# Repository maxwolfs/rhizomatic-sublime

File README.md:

# The rhizomatic sublime
### Searching for aesthetic transcendence in digital transience
Process and documentation of a research by [Max Wolfs](https://github.com/maxwolfs) and [Alexander Lehmann](https://github.com/bsplt).

### Rhizm

We object to the mundane paradigm of Human-Computer-Interaction and demand a Human-Human-Interaction. It's pyhsicial, it's intimate, it's exciting. Rhizm is a device in the shape of a credit card that connects over a satisfying magnetic click. Caution: Hands may touch. The connection of two cards creates a new bond in a decentralized social mesh network. Combined with a web interface that shows the verified encrypted interactions, Rhizm can be used for many different scenarios in which a physicial interaction between nodes must be safe. Or appealing. We understand our project as fundamental research in times of disbelief and scepsis among the realms of new technologies and social media. We want to commit ourselves to the power of open source platforms. Through social sandboxes like Rhizm a diverse variety of use cases such as self deployable social networks depending on real human interactions are possible.

Inject - Exhaust - Dissipate

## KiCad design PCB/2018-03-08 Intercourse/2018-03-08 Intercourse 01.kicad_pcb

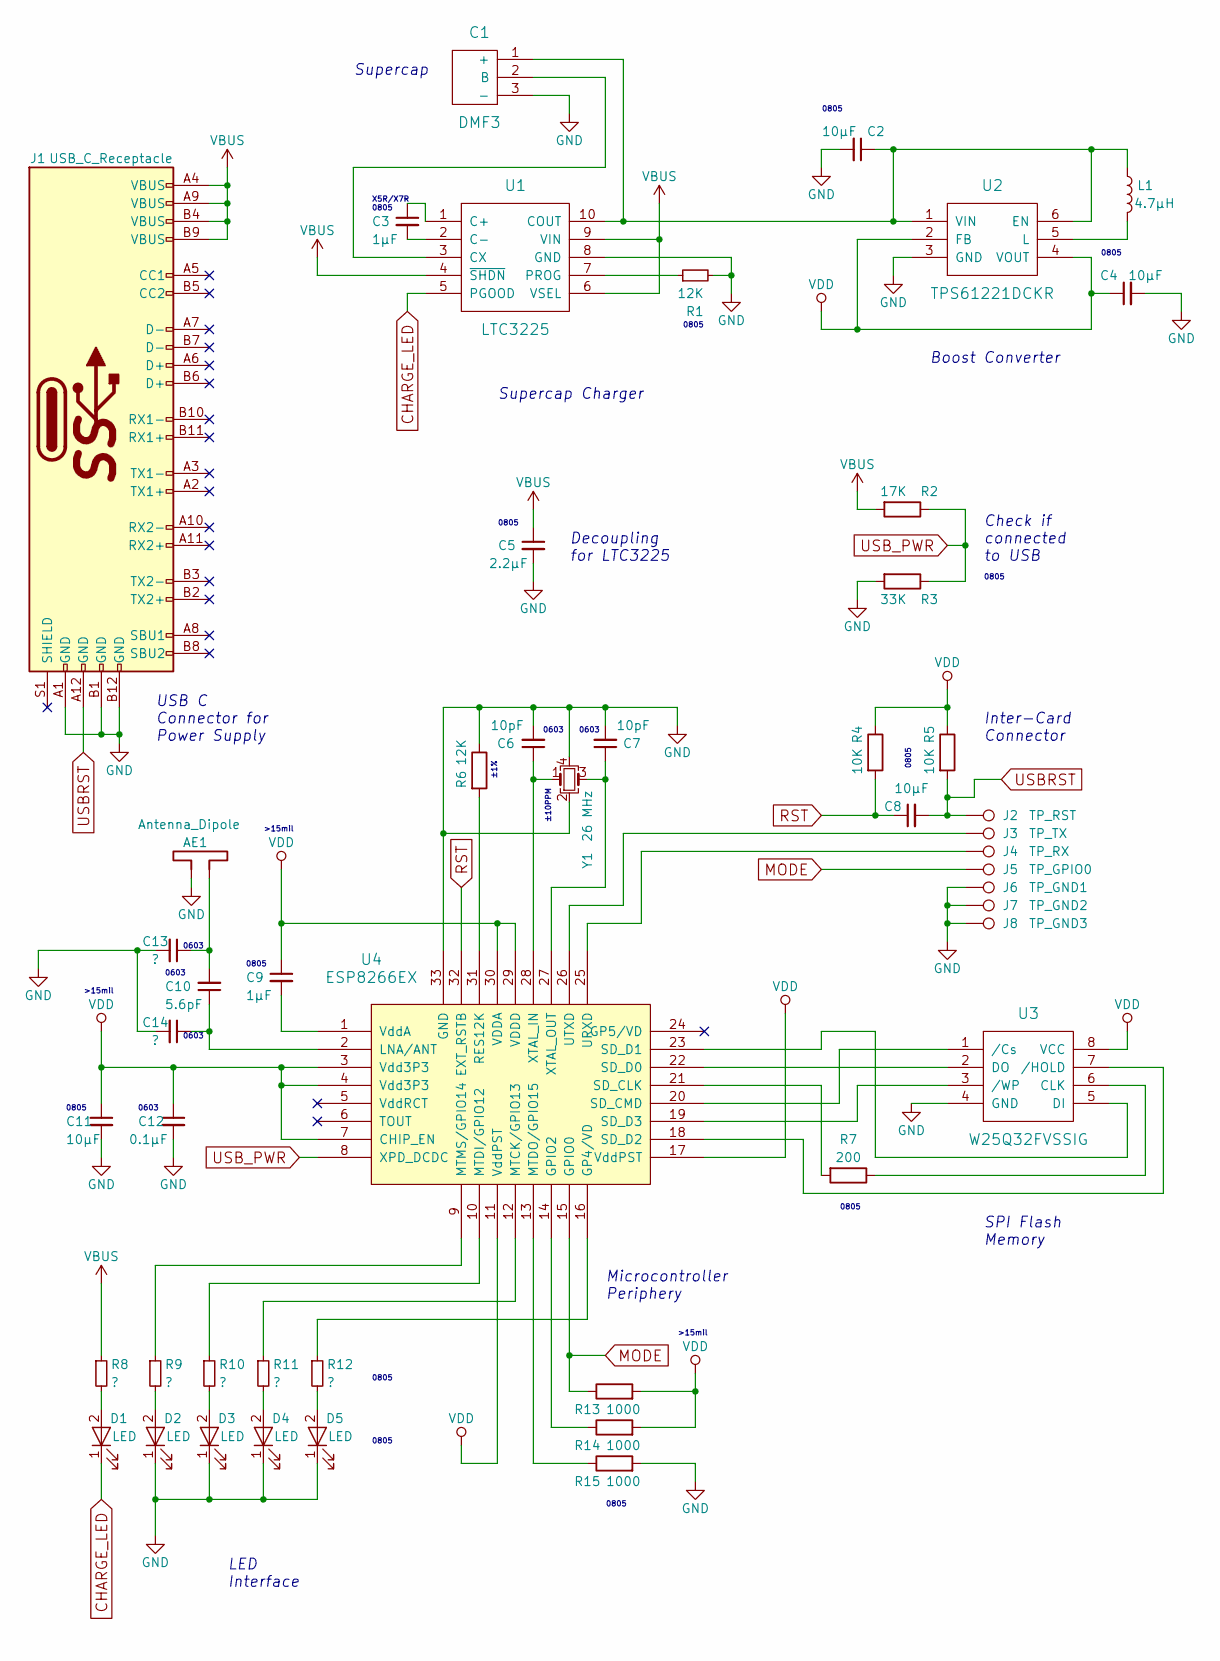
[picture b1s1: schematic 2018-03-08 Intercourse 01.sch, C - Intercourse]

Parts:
AE1: Antenna_Dipole; AN91445_47_mils
C1: DMF3; Murata_DMF3Z
C2, C4, C8, C11: 10μF; C_0805_HandSoldering
C3: 1μF; C_0805_HandSoldering
C5: 2.2μF; C_0805_HandSoldering
C6, C7: 10pF; C_0603_HandSoldering
C9: 1μF; C_0603_HandSoldering
C10: 5.6pF; C_0603_HandSoldering
C12: 0.1μF; C_0603_HandSoldering
C13, C14: ?; C_0603_1608Metric_Pad1.05x0.95mm_HandSolder
D1, D2, D3, D4, D5: LED; LED_0805_HandSoldering
J1: USB_C_Receptacle; USB_C_Receptacle_Amphenol_12401610E4-2A
J2: TP_RST; C_Connector_2mm
J3: TP_TX; C_Connector_2mm
J4: TP_RX; C_Connector_2mm
J5: TP_GPIO0; Measurement_Point_Round-SMD-Pad_Small
J6: TP_GND1; C_Connector_2mm
J7: TP_GND2; C_Connector_2mm
J8: TP_GND3; C_Connector_2mm
L1: 4.7μH; LQH3NPN4R7MJRL
R1, R6: 12K; R_0805_HandSoldering
R2: 17K; R_0805_HandSoldering
R3: 33K; R_0805_HandSoldering
R4, R5: 10K; R_0805_HandSoldering
R7: 200; R_0805_HandSoldering
R8, R9, R10, R11, R12: ?; R_0805_HandSoldering
R13, R14, R15: 1000; R_0805_HandSoldering
U1: LTC3225; DFN-10-1EP_2x3mm_Pitch0.5mm
U2: TPS61221DCKR; sc_70-6
U3: W25Q32FVSSIG; SOIC-8_3.9x4.9mm_Pitch1.27mm
U4: ESP8266EX; QFN-32-1EP_5x5mm_Pitch0.5mm
Y1: 26 MHz; Crystal_SMD_Abracon_ABM8G-4pin_3.2x2.5mm

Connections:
CHARGE_LED: D1.1 (K), U1.5 (PGOOD)
GND: AE1.1, C1.3 (-), C2.2, C4.2, C5.2, C6.2, C7.2, C11.2, C12.2, C13.2, C14.2, D2.1 (K), D3.1 (K), D4.1 (K), D5.1 (K), J1.A1 (GND), J1.B1 (GND), J1.B12 (GND), J6.1, J7.1, J8.1, R1.2, R3.2, R6.1, R15.2, U1.8 (GND), U2.3 (GND), U3.4 (GND), U4.33 (GND), Y1.2, Y1.4
MODE: J5.1, R13.1, U4.15 (GPIO0)
unnamed: AE1.2, C10.2, C13.1
unnamed: C1.1 (+), C2.1, L1.1, U1.10 (COUT), U2.1 (VIN), U2.6 (EN)
unnamed: C1.2 (B), U1.3 (CX)
unnamed: C3.1, U1.1 (C+)
unnamed: C3.2, U1.2 (C-)
unnamed: C6.1, U4.28 (XTAL_IN), Y1.1
unnamed: C7.1, U4.27 (XTAL_OUT), Y1.3
unnamed: C9.2, U4.1 (VddA)
unnamed: C10.1, C14.1, U4.2 (LNA/ANT)
unnamed: D1.2 (A), R8.2
unnamed: D2.2 (A), R9.2
unnamed: D3.2 (A), R10.2
unnamed: D4.2 (A), R11.2
unnamed: D5.2 (A), R12.2
unnamed: J3.1, U4.26 (UTXD)
unnamed: J4.1, U4.25 (URXD)
unnamed: L1.2, U2.5 (L)
unnamed: R1.1, U1.7 (PROG)
unnamed: R6.2, U4.31 (RES12K)
unnamed: R7.1, U3.6 (CLK)
unnamed: R7.2, U4.21 (SD_CLK)
unnamed: R9.1, U4.9 (MTMS/GPIO14)
unnamed: R10.1, U4.10 (MTDI/GPIO12)
unnamed: R11.1, U4.12 (MTCK/GPIO13)
unnamed: R12.1, U4.16 (GP4/VD)
unnamed: R14.1, U4.14 (GPIO2)
unnamed: R15.1, U4.13 (MTDO/GPIO15)
unnamed: U3.1 (/Cs), U4.20 (SD_CMD)
unnamed: U3.2 (DO), U4.22 (SD_D0)
unnamed: U3.3 (/WP), U4.19 (SD_D3)
unnamed: U3.5 (DI), U4.23 (SD_D1)
unnamed: U3.7 (/HOLD), U4.18 (SD_D2)
RST: C8.1, R4.2, U4.32 (EXT_RSTB)
USBRST: C8.2, J1.A12 (GND), J2.1, R5.2
USB_PWR: R2.1, R3.1, U4.8 (XPD_DCDC)
VBUS: C5.1, J1.A4 (VBUS), J1.A9 (VBUS), J1.B4 (VBUS), J1.B9 (VBUS), R2.2, R8.1, U1.4 (~SHDN), U1.6 (VSEL), U1.9 (VIN)
VDD: C4.1, C9.1, C11.1, C12.1, R4.1, R5.1, R13.2, R14.2, U2.2 (FB), U2.4 (VOUT), U3.8 (VCC), U4.3 (Vdd3P3), U4.4 (Vdd3P3), U4.7 (CHIP_EN), U4.11 (VddPST), U4.17 (VddPST), U4.29 (VDDD), U4.30 (VDDA)

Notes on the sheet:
Decoupling for LTC3225
Supercap Charger
Boost Converter
USB C Connector for Power Supply
Supercap
Microcontroller Periphery
SPI Flash Memory
Inter-Card Connector
Check if connected to USB
LED Interface
0805
±10PPM
±1%
>15mil
0603
0805
X5R/X7R 0805

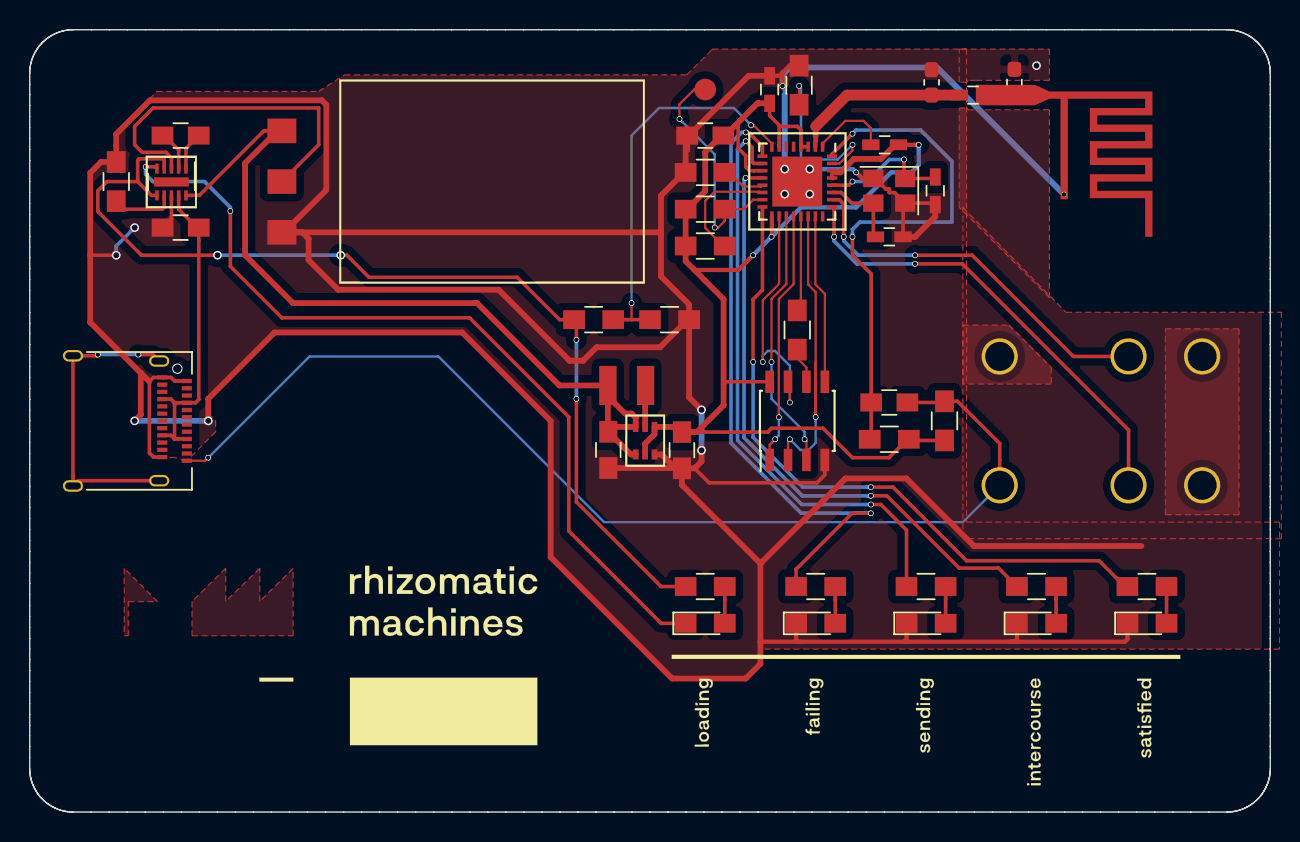
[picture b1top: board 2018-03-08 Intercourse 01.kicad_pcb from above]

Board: 2 copper layers, 85.6 x 54.0 mm, 49 parts (0 on the bottom side), 40 nets.

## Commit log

2017-07-03 :circus_tent: Added .gitattributes
2017-07-03 First TXT
2017-07-03 REWRITE readme
2017-07-03 Modified
2017-07-03 Modification
2017-07-03 Structure
2017-07-03 Minor changes and content update
2017-07-03 typo
2017-07-09 small issues
2017-07-11 english and link
2017-07-11 added idea
2017-07-11 typos
2017-07-11 subtle change
2017-07-11 added link
2017-07-19 Create Kunst oder Cash Concept
2017-07-19 Rename Kunst oder Cash to Kunst oder Cash.md
2017-07-19 Update Link & Title: Kunst oder Cash
2017-08-02 Create dystopianFuture.md
    Random Thoughts w.i.p.
2017-10-16 backup
2017-10-16 Create genesis
2017-10-16 change
2017-10-16 images
2017-10-24 UPDATE: Folder Strtucture and Link List
2017-10-24 link
2017-10-24 UPDATE: AI Trojan Horse Idea
2017-10-24 ADD Pdf proposal
2017-10-27 ADD HEC Sponsorship & Nitinol Tech Infos
2017-10-27 mpu test
2017-10-27 proposals
2017-10-31 ADD Nitinol Link
2017-11-01 new links
2017-11-01 removed conflicts
2017-11-07 ADD tech link
2017-11-10 New Link
2017-11-14 joints
2017-11-14 tree stuff links
2017-11-14 hello?
2017-11-26 NN Sim 1
2017-12-01 update links
2018-02-28 Update Budget
2018-03-07 created BOM
2018-03-07 updated BOM
2018-03-08 Add links
2018-03-08 Add Kicad Project
2018-03-13 Update Schematics
    * Add SPI Wiring
2018-03-13 Update Schematics
    * Finish ESP8266EX
2018-03-13 added spi flash
2018-03-13 Update
    Add Hardware Reference Sheet
2018-03-13 added supercap
2018-03-13 added usb
2018-03-14 Equation link
2018-03-15 added supercap charger
2018-03-15 added charge pump into schematic
2018-03-15 Update Schematic
    * Add missing Cap Values
2018-03-15 charge pump done
2018-03-15 added boost converter
2018-03-16 added TPS61221DCKR
2018-03-16 added booster circuit to schematic
2018-03-16 layout
2018-03-16 plain schematic finished and beautified
2018-03-17 link to programming resource
2018-03-17 started adding dev and conn pins
    not complete
2018-03-19 schematic edits
    * added NCs
    * clean up
2018-03-19 clean up schematic
    * added connector
    * changed labels
    * made some stuff cleaner
2018-03-19 further cleaning
    * cleaned up
    * added todos
2018-03-19 added examle for ESP8266 schematic
2018-03-20 changes labels
    Because I like them better ...
2018-03-20 added todo list
2018-03-21 added design link
2018-03-21 added reset rc filter circuit
2018-03-21 added leds to schematic
2018-03-21 added usb c recaptable
2018-03-21 Add links for writing to FLASH / EEPROM
2018-03-21 Replace BOM Table with Mouser BOM Link
2018-03-21 changed open drain circuit on charger
2018-03-21 corrected capacitors on esp8266ex
2018-03-21 minor fixes
2018-03-22 added esp8266 pin references
2018-03-22 finailzed schematic with annotations
2018-03-22 Update Paths
2018-03-22 Add Antenna Library
2018-03-22 updated library paths
2018-03-22 created additional footprints and completed footprint reference
2018-03-23 created netlist and created pcb
2018-03-23 Add Design Layout Template
2018-03-23 printability
2018-03-23 Add Max Design
2018-03-23 Add PDF Design
2018-03-23 alex sein design
2018-03-23 plotted schematic
2018-03-23 started pcb layout
2018-03-23 Add Logo AI #nocad
2018-03-24 backup of layouting process
2018-03-24 added link to kicad designing
2018-03-24 backup pcb layout
2018-03-25 advanced layout, backuping
2018-03-25 ready to route
2018-03-26 layout 01 before drc
2018-03-26 drc complete
2018-03-27 created graphic layout and edited it into pcb
2018-03-27 logo fix
2018-03-27 gerber files
2018-03-27 don't know what I changed
2018-03-30 generative experiment 1
2018-03-31 update and clean up
    deleted deprecated tables
2018-03-31 started seroius logo sketches
2018-03-31 major cleanup and moving around
2018-03-31 deleted unnecessary files
2018-03-31 explanation
2018-04-07 FIX 2 PCBnew Errors
    * Supercap + -> Henry
    * SupercapCharger GND Connection
2018-04-09 fonts
2018-04-09 layouten
2018-04-09 clean pcb is fine
2018-04-09 added layout and created gerber files
2018-04-10 Add USBRST Connection on .sch & .pcb
2018-04-10 rev3
2018-04-10 rev3 fixed via position
2018-04-11 Add Test Code
2018-04-12 Update Links
    * Add RF PCB Guidelines Link
2018-04-15 Add esp-http-post code
2018-04-16 Dataviz and Clean Up
2018-04-16 Update Readme and demo esp code
2018-04-17 Update Presentation Code
2018-04-18 Add Brochure
2018-04-18 dataviz looks good!
2018-04-18 cleanup and presentation
2018-04-19 backup and fixes
2018-04-19 Add userflow
2018-04-19 broschure
2018-04-19 ausgeschossen
2018-04-20 notizen
2018-04-20 Update Codes
2018-04-22 Add HEC application
2018-04-22 flowchart
2018-04-22 edit
2018-04-22 application pdf
2018-05-08 update brochure folder
2018-05-08 Add conference document
2018-05-08 change title
2018-05-08 Auto stash before merge of "master" and "origin/master"
2018-05-08 cleanup
2018-05-08 Conference
2018-05-08 updatze
2018-05-25 Add web documentation
2018-05-27 add conference pptx
2018-08-08 update scenarios
2018-11-10 update presentation
2018-11-22 update foto
2018-11-22 presentation backup
2018-11-22 update ppt
2018-11-23 add kicad screen
2019-05-19 update and antenna
    - drawn antenna component and footprint
    - backup before changing the schematics and layout
2019-05-19 updated antenna design
    board ready for revision
2019-05-20 updated antenna design
    - had to move components also
2019-05-23 rev4 ready for review
    - added parts to antenna trace
    - created gerber files
2019-06-13 bom & pos files
